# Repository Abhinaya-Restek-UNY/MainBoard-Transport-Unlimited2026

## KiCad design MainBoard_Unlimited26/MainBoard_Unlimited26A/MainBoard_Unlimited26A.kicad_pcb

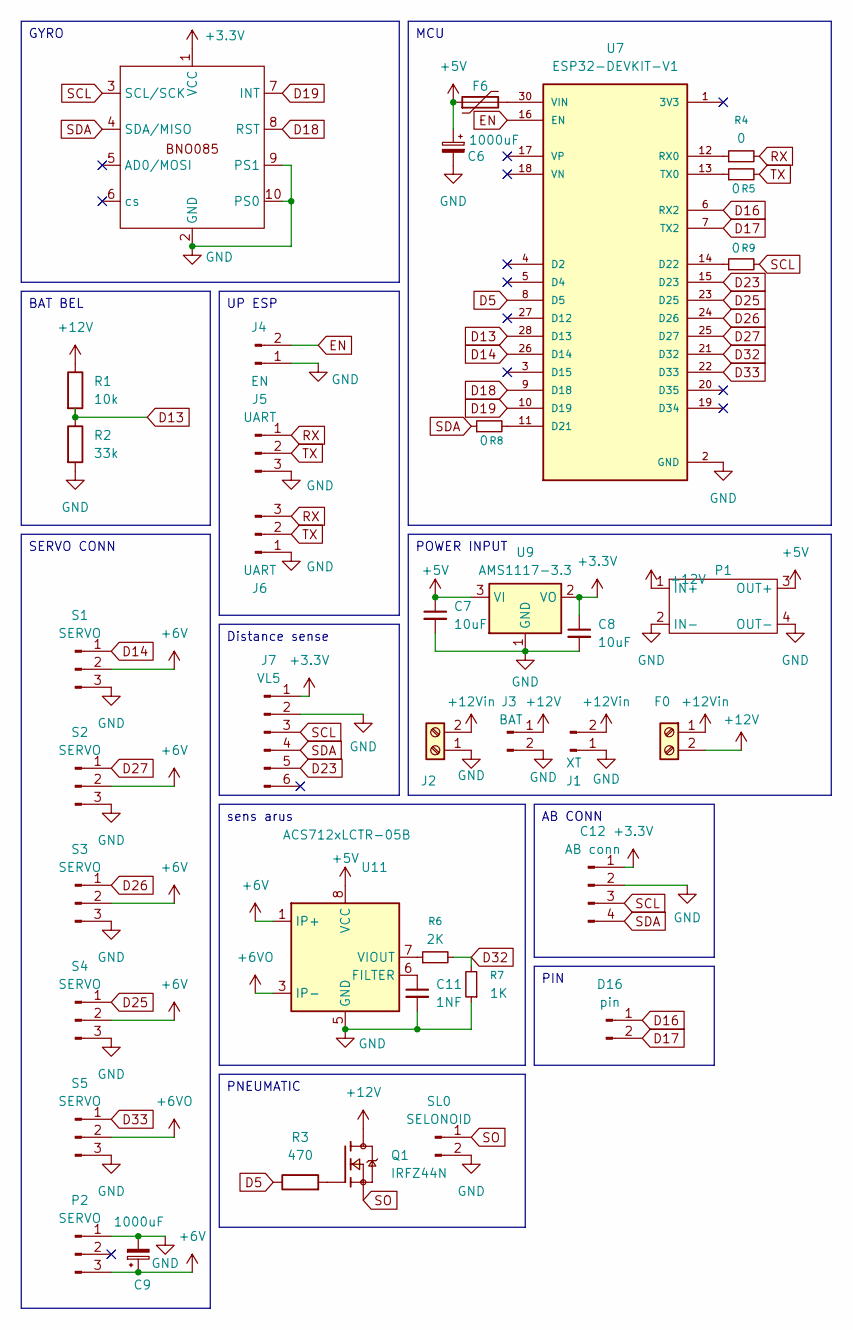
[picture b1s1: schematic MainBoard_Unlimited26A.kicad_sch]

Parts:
C6, C9: 1000uF; CP_Radial_D10.0mm_P5.00mm
C7, C8: 10uF; C_0805_2012Metric_Pad1.18x1.45mm_HandSolder
C11: 1NF; C_0805_2012Metric_Pad1.18x1.45mm_HandSolder
C12: AB conn; JST_XH_S4B-XH-A-1_1x04_P2.50mm_Horizontal
D16: pin; PinHeader_1x02_P2.54mm_Vertical
F0: Screw_Terminal_01x02; TerminalBlock_MaiXu_MX126-5.0-02P_1x02_P5.00mm
F6: Polyfuse; Fuse_1812_4532Metric
J1: XT; AMASS_XT60-M_1x02_P7.20mm_Vertical
J2: Screw_Terminal_01x02; TerminalBlock_MaiXu_MX126-5.0-02P_1x02_P5.00mm
J3: BAT; JST_XH_B2B-XH-A_1x02_P2.50mm_Vertical
J4: EN; PinHeader_1x02_P2.54mm_Horizontal
J5: UART; PinHeader_1x03_P2.54mm_Horizontal
J6: UART; JST_XH_S3B-XH-A_1x03_P2.50mm_Horizontal
J7: VL5; JST_XH_B6B-XH-A_1x06_P2.50mm_Vertical
P1: MP1584_Module
P2: SERVO; JST_XH_B3B-XH-A_1x03_P2.50mm_Vertical
Q1: IRFZ44N; TO254P1016X419X2286-3; PARTREV 09/21/10
R1: 10k; R_1206_3216Metric_Pad1.30x1.75mm_HandSolder
R2: 33k; R_0805_2012Metric_Pad1.20x1.40mm_HandSolder
R3: 470; R_1206_3216Metric_Pad1.30x1.75mm_HandSolder
R4, R5, R8, R9: 0; R_1206_3216Metric_Pad1.30x1.75mm_HandSolder
R6: 2K; R_0805_2012Metric_Pad1.20x1.40mm_HandSolder
R7: 1K; R_0805_2012Metric_Pad1.20x1.40mm_HandSolder
S1, S2, S3, S4, S5: SERVO; JST_XH_B3B-XH-A_1x03_P2.50mm_Vertical
SL0: SELONOID; JST_XH_B2B-XH-A_1x02_P2.50mm_Vertical
U7: ESP32-DEVKIT-V1; MODULE_ESP32_DEVKIT_V1; PARTREV N/A
U8: MPU6050/BNO085 I2C; PinSocket_1x10_P2.54mm_Vertical
U9: AMS1117-3.3; SOT-223-3_TabPin2
U11: ACS712xLCTR-05B; SOIC-8_3.9x4.9mm_P1.27mm

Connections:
+3.3V: C8.1, C12.1, J7.1, U8.1 (VCC), U9.2 (VO)
+5V: C6.1, C7.1, F6.1, P1.3 (OUT+), U9.3 (VI), U11.8 (VCC)
+6V: C9.1, P2.3, S1.2, S2.2, S3.2, S4.2, U11.1 (IP+), U11.2 (IP+)
+6VO: S5.2, U11.3 (IP-), U11.4 (IP-)
+12V: F0.2, J3.1, P1.1 (IN+), Q1.2, R1.1
+12Vin: F0.1, J1.2, J2.2
D5: R3.1, U7.8 (D5)
D13: R1.2, R2.1, U7.28 (D13)
D14: S1.1, U7.26 (D14)
D16: D16.1, U7.6 (RX2)
D17: D16.2, U7.7 (TX2)
D18: U7.9 (D18), U8.8 (RST)
D19: U7.10 (D19), U8.7 (INT)
D23: J7.5, U7.15 (D23)
D25: S4.1, U7.23 (D25)
D26: S3.1, U7.24 (D26)
D27: S2.1, U7.25 (D27)
D32: R6.2, R7.2, U7.21 (D32)
D33: S5.1, U7.22 (D33)
EN: J4.2, U7.16 (EN)
GND: C6.2, C7.2, C8.2, C9.2, C11.2, C12.2, J1.1, J2.1, J3.2, J4.1, J5.3, J6.1, J7.2, P1.2 (IN-), P1.4 (OUT-), P2.1, R2.2, R7.1, S1.3, S2.3, S3.3, S4.3, S5.3, SL0.2, U7.2 (GND), U7.29 (GND), U8.2 (GND), U8.9 (PS1), U8.10 (PS0), U9.1 (GND), U11.5 (GND)
unnamed: Q1.1, R3.2
unnamed: R8.2, U7.11 (D21)
unnamed: R9.1, U7.14 (D22)
unnamed: R4.1, U7.12 (RX0)
unnamed: R5.1, U7.13 (TX0)
unnamed: F6.2, U7.30 (VIN)
unnamed: C11.1, U11.6 (FILTER)
unnamed: R6.1, U11.7 (VIOUT)
RX: J5.1, J6.3, R4.2
SCL: C12.3, J7.3, R9.2, U8.3 (SCL/SCK)
SDA: C12.4, J7.4, R8.1, U8.4 (SDA/MISO)
SO: Q1.3, SL0.1
TX: J5.2, J6.2, R5.2

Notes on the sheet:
AB CONN
PIN
UP ESP
PNEUMATIC
sens arus
POWER INPUT
MCU
BAT BEL
Distance sense
GYRO
SERVO CONN

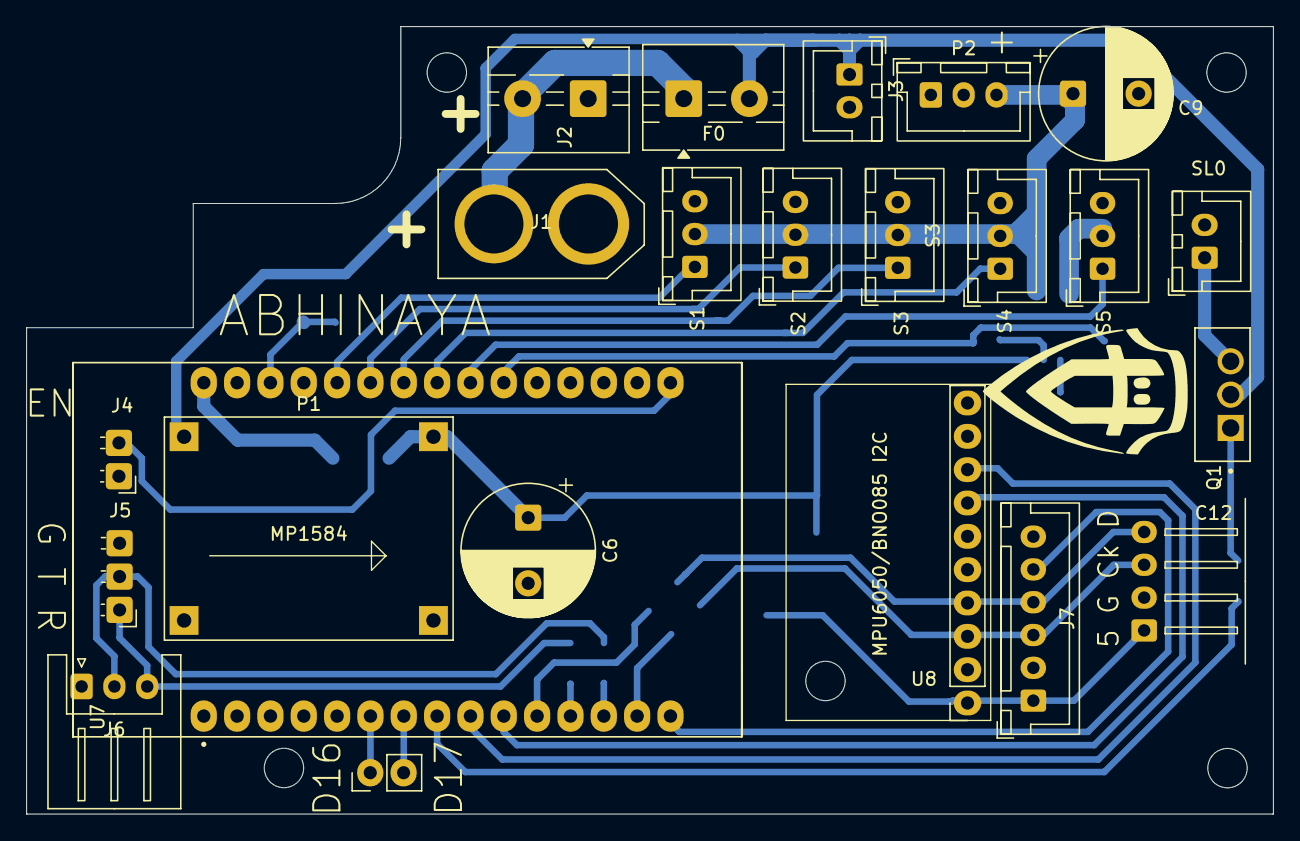
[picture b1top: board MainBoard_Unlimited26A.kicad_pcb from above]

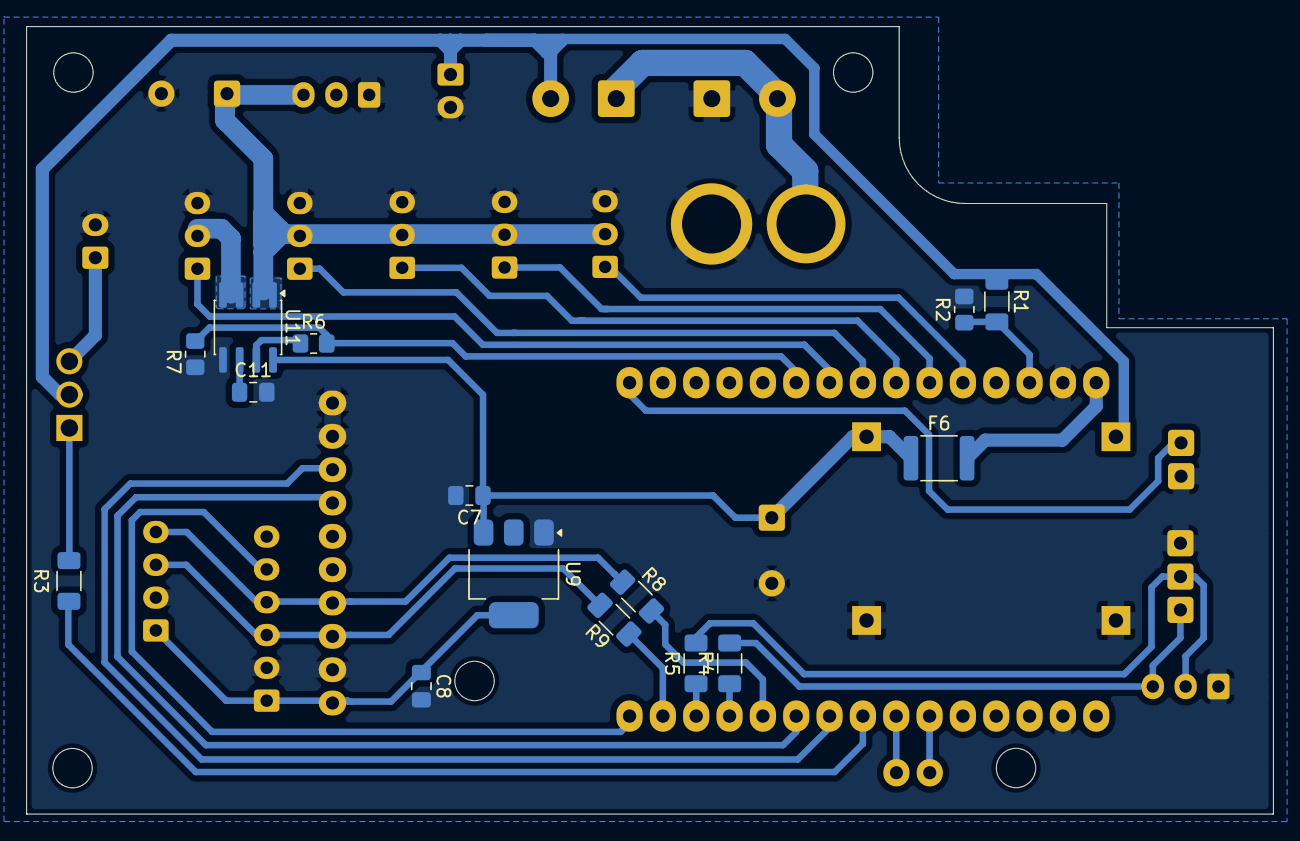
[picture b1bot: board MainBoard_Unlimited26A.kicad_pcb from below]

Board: 2 copper layers, 95.0 x 60.0 mm, 38 parts (15 on the bottom side), 34 nets.

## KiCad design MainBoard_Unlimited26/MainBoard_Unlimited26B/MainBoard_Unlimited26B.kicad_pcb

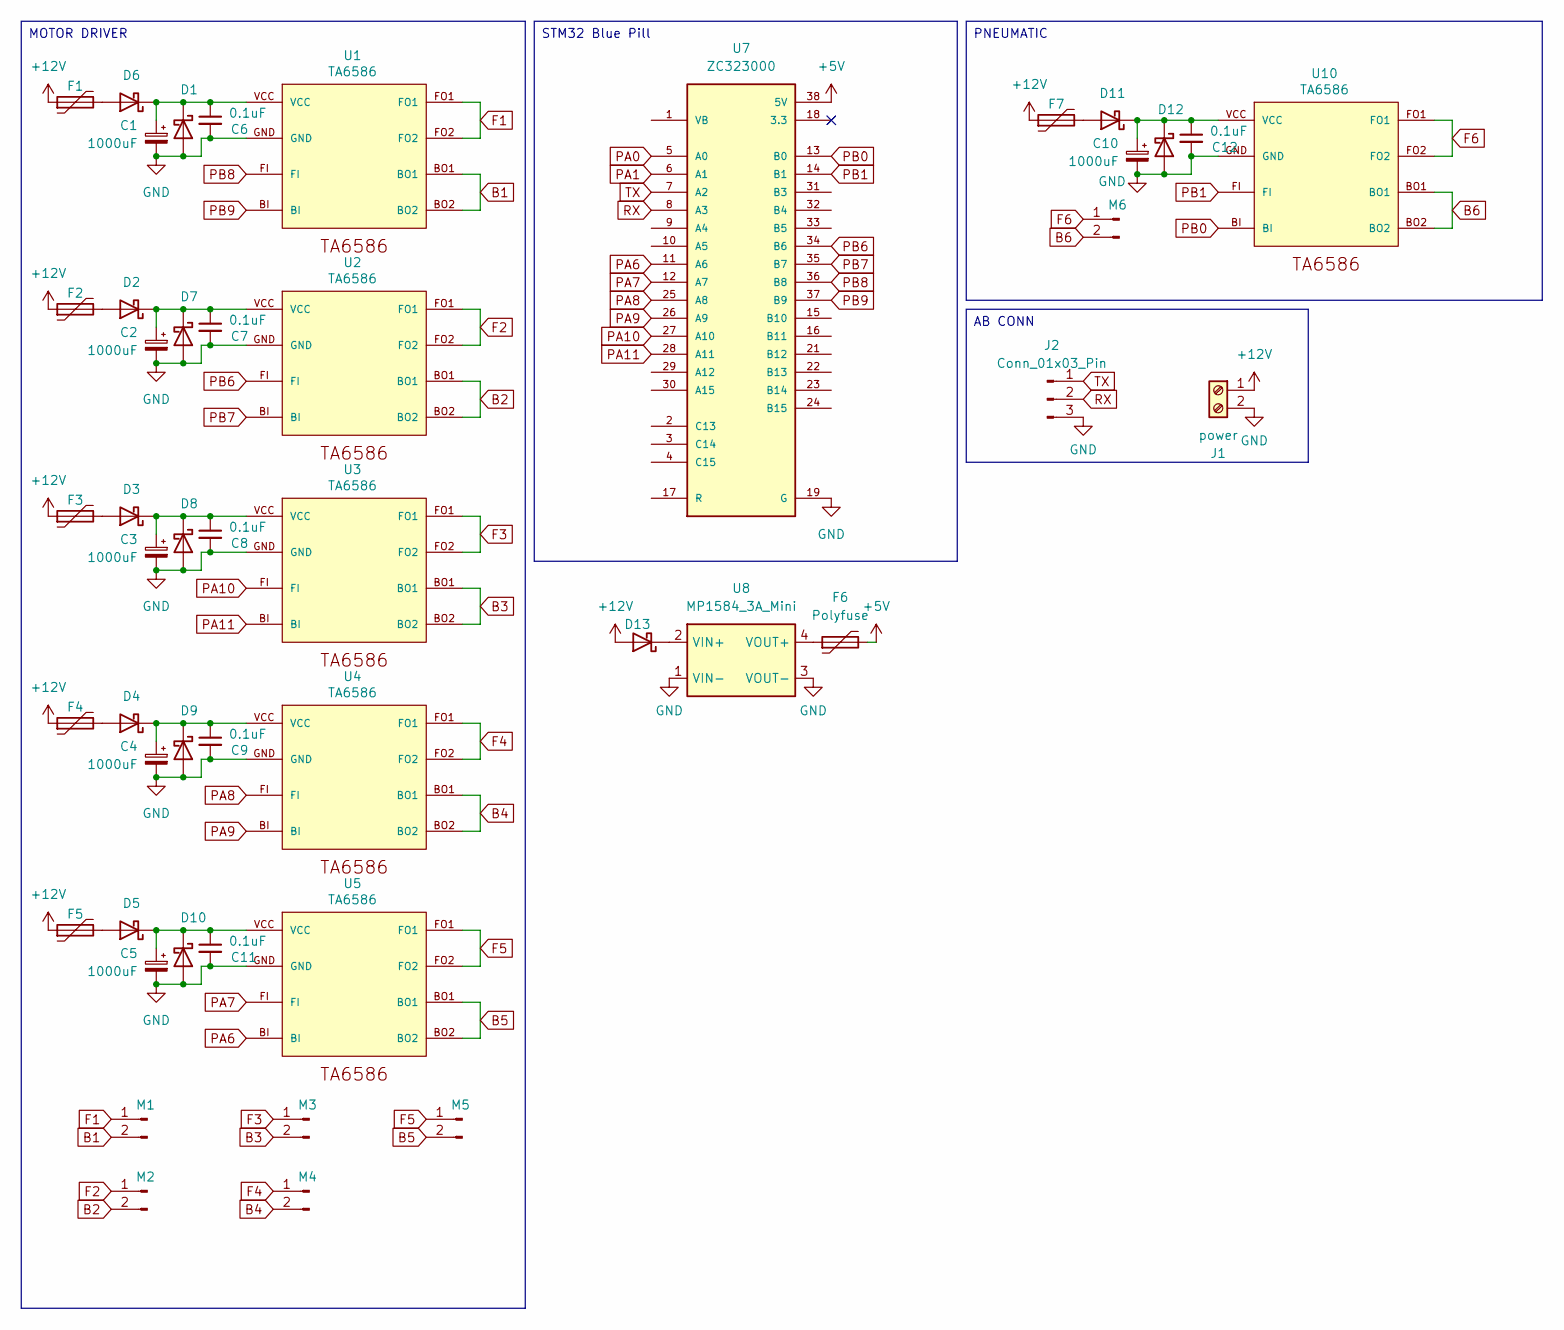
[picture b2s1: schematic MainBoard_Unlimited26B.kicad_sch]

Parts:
C1, C2, C3, C4, C5, C10: 1000uF; CP_Radial_D10.0mm_P5.00mm
C6, C7, C8, C9, C11, C12: 0.1uF; C_0805_2012Metric_Pad1.18x1.45mm_HandSolder
D1, D2, D3, D4, D5, D6, D7, D8, D9, D10, D11, D12, D13: D_Schottky; D_SMA
F1, F2, F3, F4, F5, F7: Polyfuse; Fuse_Bourns_MF-RG300
F6: Polyfuse; Fuse_1812_4532Metric
J1: power; TE_282815-2
J2: Conn_01x03_Pin; JST_XH_B3B-XH-A_1x03_P2.50mm_Vertical
M1, M2, M3, M4, M5, M6: JST_XH_S2B-XH-A-1_1x02_P2.50mm_Horizontal
U1, U2, U3, U4, U5, U10: TA6586; TA6586-FOOTPRINT
U7: ZC323000; MODULE_ZC323000; PARTREV N/A
U8: MP1584_3A_Mini; Mini360

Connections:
+5V: F6.2, U7.38 (5V)
+12V: D13.2 (A), F1.1, F2.1, F3.1, F4.1, F5.1, F7.1, J1.1
B1: M1.2, U1.BO1, U1.BO2
B2: M2.2, U2.BO1, U2.BO2
B3: M3.2, U3.BO1, U3.BO2
B4: M4.2, U4.BO1, U4.BO2
B5: M5.2, U5.BO1, U5.BO2
B6: M6.2, U10.BO1, U10.BO2
F1: M1.1, U1.FO1, U1.FO2
F2: M2.1, U2.FO1, U2.FO2
F3: M3.1, U3.FO1, U3.FO2
F4: M4.1, U4.FO1, U4.FO2
F5: M5.1, U5.FO1, U5.FO2
F6: M6.1, U10.FO1, U10.FO2
GND: C1.2, C2.2, C3.2, C4.2, C5.2, C6.2, C7.2, C8.2, C9.2, C10.2, C11.2, C12.2, D1.2 (A), D7.2 (A), D8.2 (A), D9.2 (A), D10.2 (A), D12.2 (A), J1.2, J2.3, U1.GND, U2.GND, U3.GND, U4.GND, U5.GND, U7.19 (G), U7.20 (G), U7.39 (G), U8.1 (VIN-), U8.3 (VOUT-), U10.GND
unnamed: C1.1, C6.1, D1.1 (K), D6.1 (K), U1.VCC
unnamed: D2.2 (A), F2.2
unnamed: C2.1, C7.1, D2.1 (K), D7.1 (K), U2.VCC
unnamed: D3.2 (A), F3.2
unnamed: C3.1, C8.1, D3.1 (K), D8.1 (K), U3.VCC
unnamed: D4.2 (A), F4.2
unnamed: C4.1, C9.1, D4.1 (K), D9.1 (K), U4.VCC
unnamed: D5.2 (A), F5.2
unnamed: D6.2 (A), F1.2
unnamed: C5.1, C11.1, D5.1 (K), D10.1 (K), U5.VCC
unnamed: D11.2 (A), F7.2
unnamed: C10.1, C12.1, D11.1 (K), D12.1 (K), U10.VCC
unnamed: D13.1 (K), U8.2 (VIN+)
unnamed: F6.1, U8.4 (VOUT+)
PA0: U7.5 (A0)
PA1: U7.6 (A1)
PA6: U5.BI, U7.11 (A6)
PA7: U5.FI, U7.12 (A7)
PA8: U4.FI, U7.25 (A8)
PA9: U4.BI, U7.26 (A9)
PA10: U3.FI, U7.27 (A10)
PA11: U3.BI, U7.28 (A11)
PB0: U7.13 (B0), U10.BI
PB1: U7.14 (B1), U10.FI
PB6: U2.FI, U7.34 (B6)
PB7: U2.BI, U7.35 (B7)
PB8: U1.FI, U7.36 (B8)
PB9: U1.BI, U7.37 (B9)
RX: J2.2, U7.8 (A3)
TX: J2.1, U7.7 (A2)

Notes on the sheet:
PNEUMATIC
AB CONN
MOTOR DRIVER
STM32 Blue Pill

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
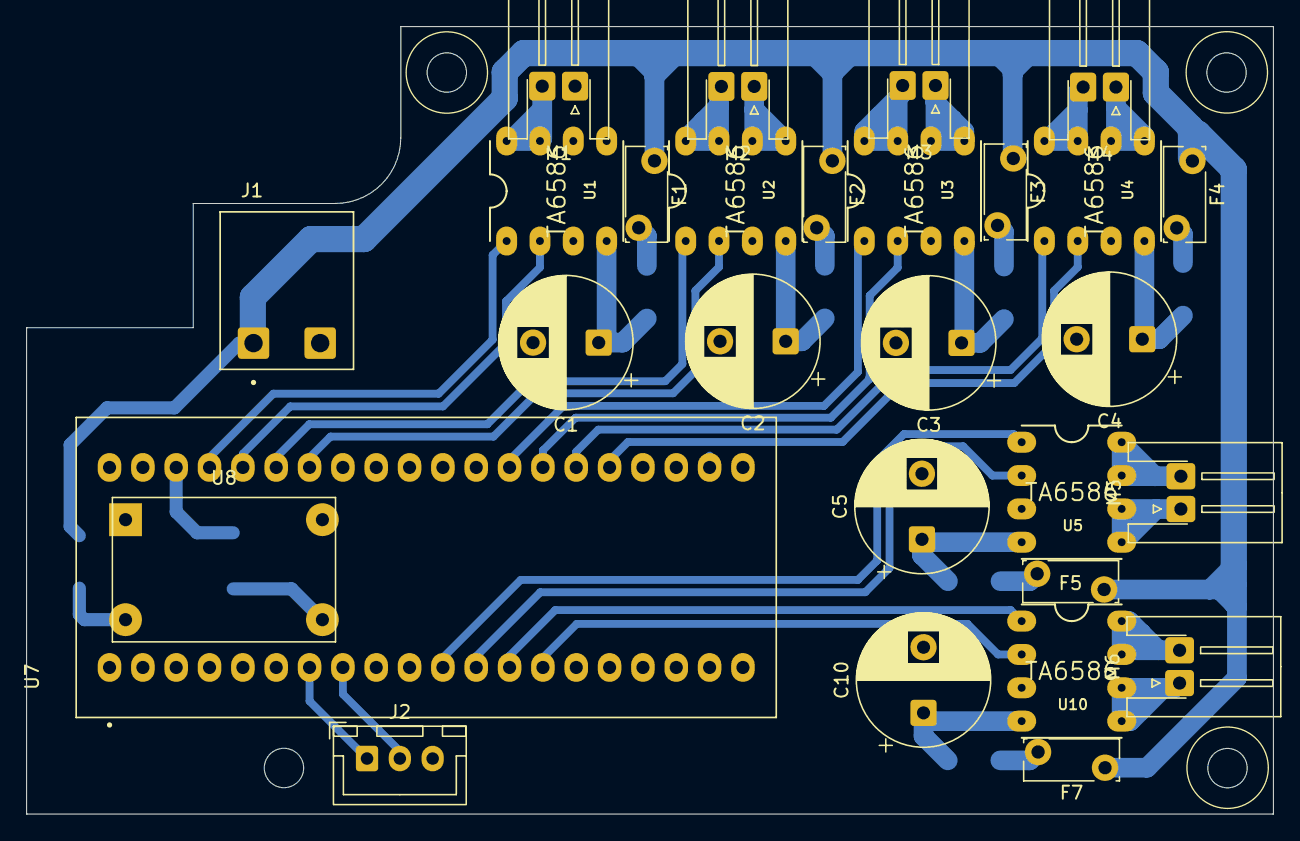
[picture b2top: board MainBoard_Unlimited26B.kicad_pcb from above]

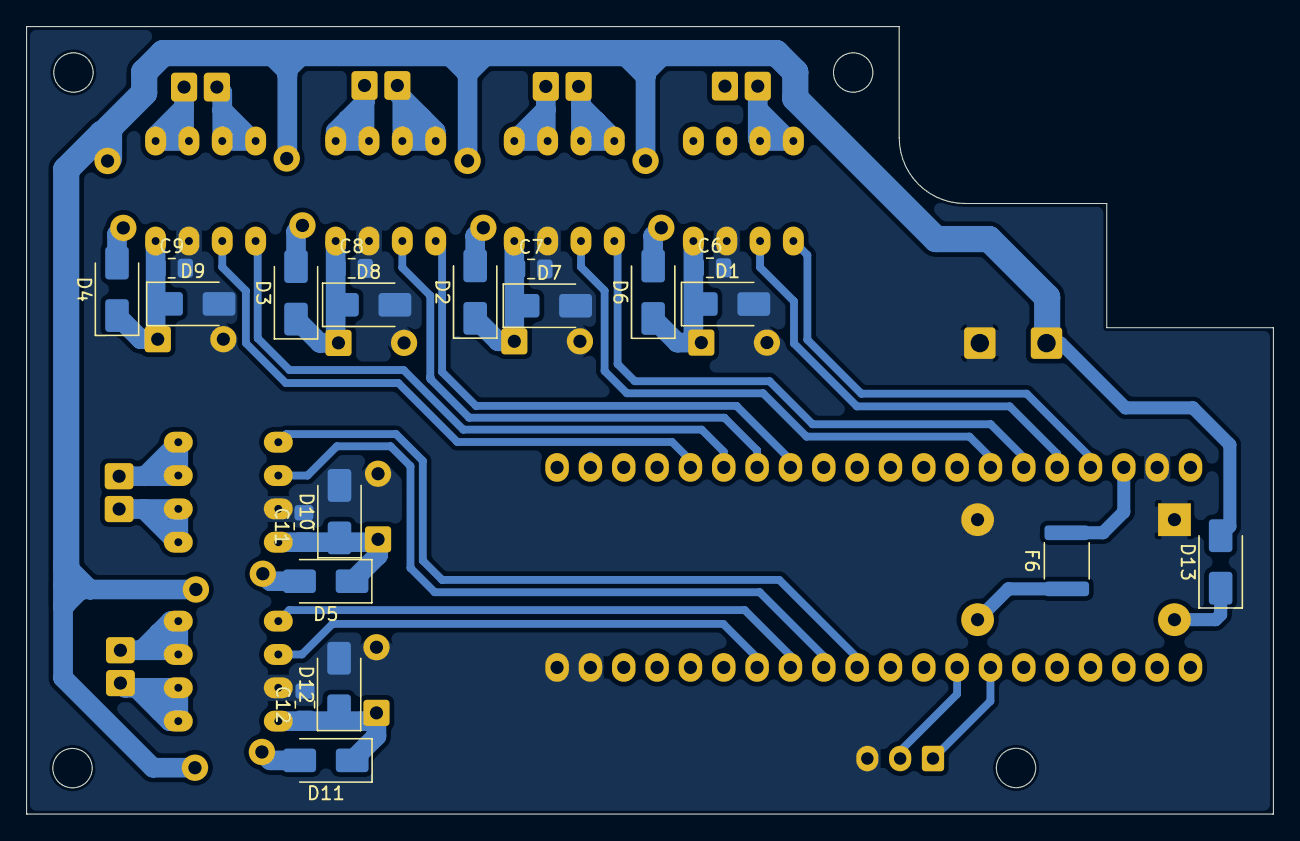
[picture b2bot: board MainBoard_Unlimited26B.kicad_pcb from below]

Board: 2 copper layers, 95.0 x 60.0 mm, 48 parts (20 on the bottom side), 43 nets.

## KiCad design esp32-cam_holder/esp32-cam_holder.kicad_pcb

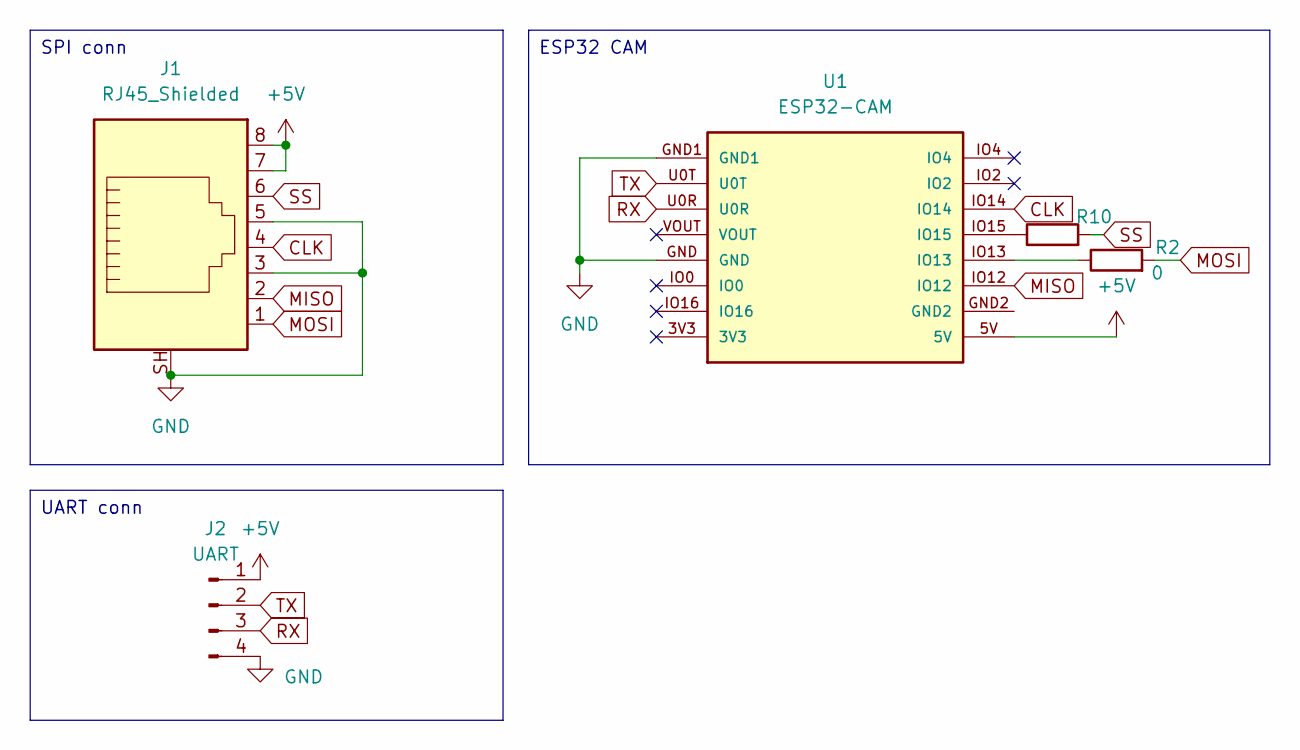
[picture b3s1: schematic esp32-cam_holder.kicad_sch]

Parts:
J1: RJ45_Shielded; RJ45_Amphenol_RJHSE5380
J2: UART; PinHeader_1x04_P2.54mm_Horizontal
R1, R2: 0; R_1206_3216Metric_Pad1.30x1.75mm_HandSolder
U1: ESP32-CAM

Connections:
+5V: J1.7, J1.8, J2.1, U1.5V
CLK: J1.4, U1.IO14
GND: J1.3, J1.5, J1.SH, J2.4, U1.GND, U1.GND1
MISO: J1.2, U1.IO12
MOSI: J1.1, R2.2
unnamed: R1.1, U1.IO15
unnamed: R2.1, U1.IO13
RX: J2.3, U1.U0R
SS: J1.6, R1.2
TX: J2.2, U1.U0T

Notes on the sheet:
ESP32 CAM
SPI conn
UART conn

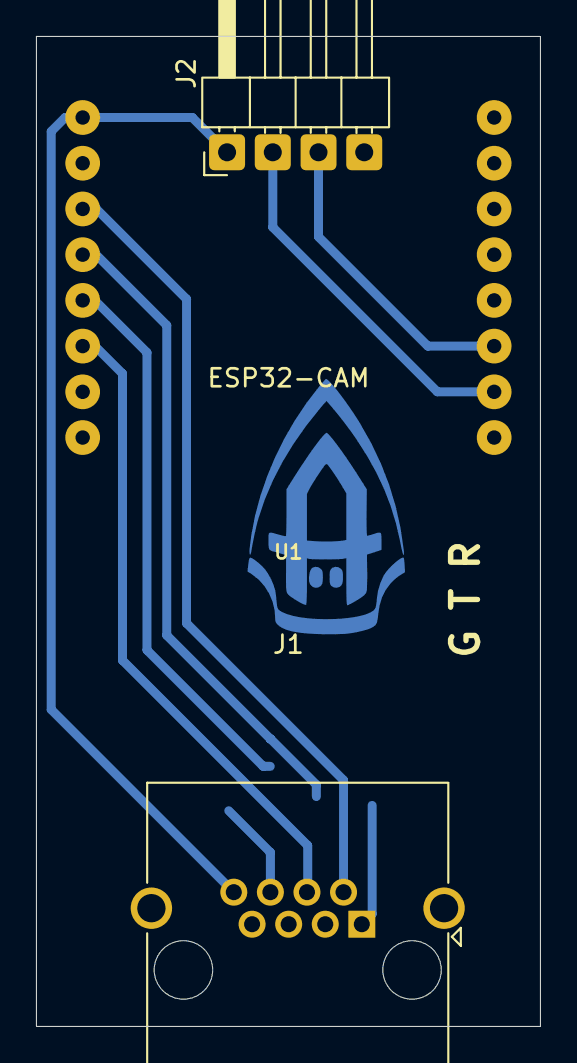
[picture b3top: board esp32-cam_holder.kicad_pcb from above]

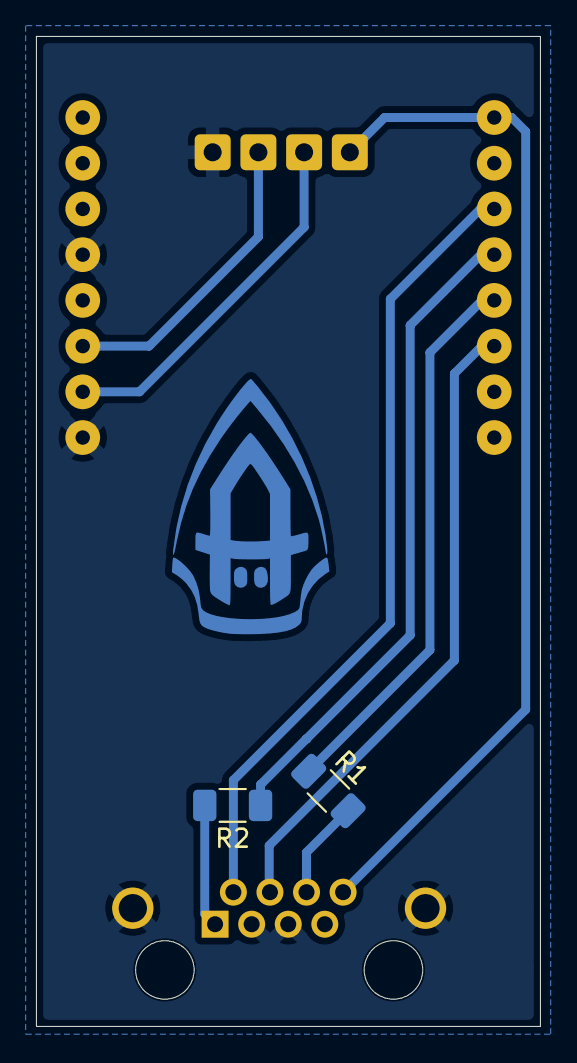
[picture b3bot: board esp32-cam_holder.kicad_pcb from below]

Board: 2 copper layers, 28.0 x 55.0 mm, 5 parts (2 on the bottom side), 10 nets.

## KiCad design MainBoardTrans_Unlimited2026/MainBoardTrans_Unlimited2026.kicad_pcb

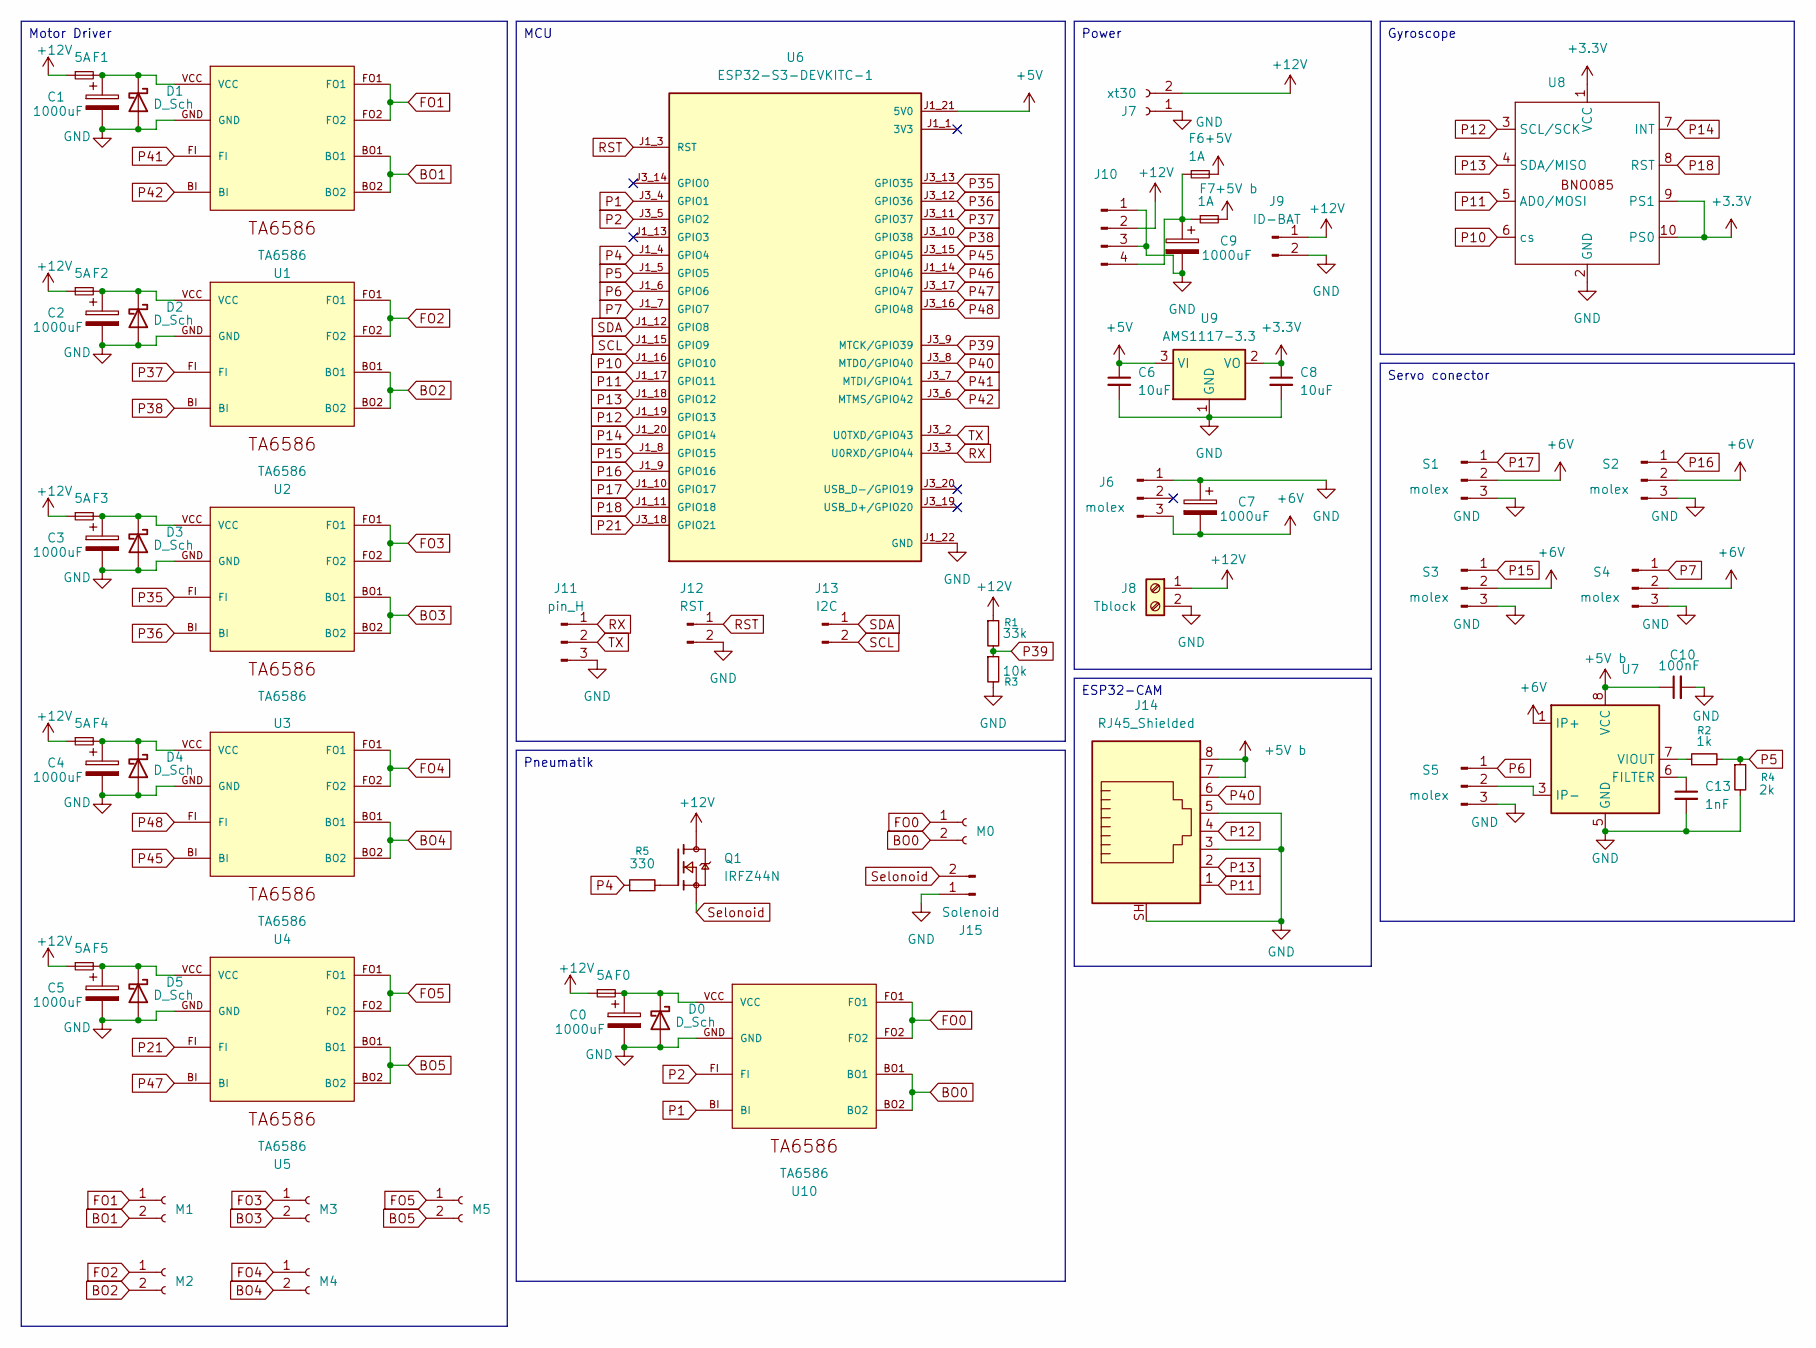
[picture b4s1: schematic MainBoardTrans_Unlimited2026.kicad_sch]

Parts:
C0, C1, C2, C3, C4, C5, C7, C9: 1000uF; CP_Radial_D10.0mm_P5.00mm
C6, C8: 10uF; C_0805_2012Metric_Pad1.18x1.45mm_HandSolder
C10: 100nF; C_0805_2012Metric_Pad1.18x1.45mm_HandSolder
C13: 1nF; C_0805_2012Metric_Pad1.18x1.45mm_HandSolder
D0, D1, D2, D3, D4, D5: D_Sch; D_SMA_Handsoldering
F0, F1, F2, F3, F4, F5: 5A; Fuse_Bourns_MF-RHT300
F6, F7: 1A; Fuse_1812_4532Metric
J6: molex; JST_XH_B3B-XH-A_1x03_P2.50mm_Vertical
J7: xt30; AMASS_XT30U-M_1x02_P5.0mm_Vertical
J8: Tblock; TerminalBlock_MaiXu_MX126-5.0-02P_1x02_P5.00mm
J9: ID-BAT; JST_XH_B2B-XH-A_1x02_P2.50mm_Vertical
J10: DSN-MINI-360; Mini360
J11: pin_H; PinHeader_1x03_P2.54mm_Horizontal
J12: RST; JST_XH_B2B-XH-A_1x02_P2.50mm_Vertical
J13: I2C; PinHeader_1x02_P2.54mm_Vertical
J14: RJ45_Shielded; RJ45_Amphenol_RJHSE5380
J15: Solenoid; JST_XH_B2B-XH-A_1x02_P2.50mm_Vertical
M0, M1, M2, M3, M4, M5: TerminalBlock_MaiXu_MX126-5.0-02P_1x02_P5.00mm
Q1: IRFZ44N; TO254P1016X419X2286-3; PARTREV 09/21/10
R1: 33k; R_Axial_DIN0207_L6.3mm_D2.5mm_P10.16mm_Horizontal
R2: 1k; R_0805_2012Metric_Pad1.20x1.40mm_HandSolder
R3: 10k; R_Axial_DIN0207_L6.3mm_D2.5mm_P10.16mm_Horizontal
R4: 2k; R_0805_2012Metric_Pad1.20x1.40mm_HandSolder
R5: 330; R_1206_3216Metric_Pad1.30x1.75mm_HandSolder
S1, S2, S3, S4, S5: molex; JST_XH_B3B-XH-A_1x03_P2.50mm_Vertical
U1, U2, U3, U4, U5, U10: TA6586; TA6586-FOOTPRINT
U6: ESP32-S3-DEVKITC-1; XCVR_ESP32-S3-DEVKITC-1-N32R8V; PARTREV 1.1
U7: ACS712xLCTR-05B; SOIC-8_3.9x4.9mm_P1.27mm
U8: BNO085
U9: AMS1117-3.3; SOT-223-3_TabPin2

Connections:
+3.3V: C8.1, U8.1 (VCC), U8.9 (PS1), U8.10 (PS0), U9.2 (VO)
+5V: C6.1, F6.2, U6.J1_21 (5V0), U9.3 (VI)
+5V b: C10.1, F7.2, J14.7, J14.8, U7.8 (VCC)
+6V: C7.2, J6.3, S1.2, S2.2, S3.2, S4.2, U7.1 (IP+), U7.2 (IP+)
+12V: F0.1, F1.1, F2.1, F3.1, F4.1, F5.1, J7.2, J8.1, J9.1, J10.2, Q1.2, R1.1
BO0: M0.2, U10.BO1, U10.BO2
BO1: M1.2, U1.BO1, U1.BO2
BO2: M2.2, U2.BO1, U2.BO2
BO3: M3.2, U3.BO1, U3.BO2
BO4: M4.2, U4.BO1, U4.BO2
BO5: M5.2, U5.BO1, U5.BO2
FO0: M0.1, U10.FO1, U10.FO2
FO1: M1.1, U1.FO1, U1.FO2
FO2: M2.1, U2.FO1, U2.FO2
FO3: M3.1, U3.FO1, U3.FO2
FO4: M4.1, U4.FO1, U4.FO2
FO5: M5.1, U5.FO1, U5.FO2
GND: C0.2, C1.2, C2.2, C3.2, C4.2, C5.2, C6.2, C7.1, C8.2, C9.2, C10.2, C13.2, D0.2 (A), D1.2 (A), D2.2 (A), D3.2 (A), D4.2 (A), D5.2 (A), J6.1, J7.1, J8.2, J9.2, J10.1, J10.3, J11.3, J12.2, J14.3, J14.5, J14.SH, J15.1, R3.2, R4.2, S1.3, S2.3, S3.3, S4.3, S5.3, U1.GND, U2.GND, U3.GND, U4.GND, U5.GND, U6.J1_22 (GND), U6.J3_1 (GND), U6.J3_21 (GND), U6.J3_22 (GND), U7.5 (GND), U8.2 (GND), U9.1 (GND), U10.GND
unnamed: C0.1, D0.1 (K), F0.2, U10.VCC
unnamed: C1.1, D1.1 (K), F1.2, U1.VCC
unnamed: C2.1, D2.1 (K), F2.2, U2.VCC
unnamed: C3.1, D3.1 (K), F3.2, U3.VCC
unnamed: C4.1, D4.1 (K), F4.2, U4.VCC
unnamed: C5.1, D5.1 (K), F5.2, U5.VCC
unnamed: C9.1, F6.1, F7.1, J10.4
unnamed: Q1.1, R5.2
unnamed: S5.2, U7.3 (IP-), U7.4 (IP-)
unnamed: C13.1, U7.6 (FILTER)
unnamed: R2.1, U7.7 (VIOUT)
P1: U6.J3_4 (GPIO1), U10.BI
P2: U6.J3_5 (GPIO2), U10.FI
P4: R5.1, U6.J1_4 (GPIO4)
P5: R2.2, R4.1, U6.J1_5 (GPIO5)
P6: S5.1, U6.J1_6 (GPIO6)
P7: S4.1, U6.J1_7 (GPIO7)
P10: U6.J1_16 (GPIO10), U8.6 (cs)
P11: J14.1, U6.J1_17 (GPIO11), U8.5 (AD0/MOSI)
P12: J14.4, U6.J1_19 (GPIO13), U8.3 (SCL/SCK)
P13: J14.2, U6.J1_18 (GPIO12), U8.4 (SDA/MISO)
P14: U6.J1_20 (GPIO14), U8.7 (INT)
P15: S3.1, U6.J1_8 (GPIO15)
P16: S2.1, U6.J1_9 (GPIO16)
P17: S1.1, U6.J1_10 (GPIO17)
P18: U6.J1_11 (GPIO18), U8.8 (RST)
P21: U5.FI, U6.J3_18 (GPIO21)
P35: U3.FI, U6.J3_13 (GPIO35)
P36: U3.BI, U6.J3_12 (GPIO36)
P37: U2.FI, U6.J3_11 (GPIO37)
P38: U2.BI, U6.J3_10 (GPIO38)
P39: R1.2, R3.1, U6.J3_9 (MTCK/GPIO39)
P40: J14.6, U6.J3_8 (MTDO/GPIO40)
P41: U1.FI, U6.J3_7 (MTDI/GPIO41)
P42: U1.BI, U6.J3_6 (MTMS/GPIO42)
P45: U4.BI, U6.J3_15 (GPIO45)
P46: U6.J1_14 (GPIO46)
P47: U5.BI, U6.J3_17 (GPIO47)
P48: U4.FI, U6.J3_16 (GPIO48)
RST: J12.1, U6.J1_3 (RST)
RX: J11.1, U6.J3_3 (U0RXD/GPIO44)
SCL: J13.2, U6.J1_15 (GPIO9)
SDA: J13.1, U6.J1_12 (GPIO8)
Selonoid: J15.2, Q1.3
TX: J11.2, U6.J3_2 (U0TXD/GPIO43)

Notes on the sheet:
Pneumatik
Motor Driver
Gyroscope
MCU
Servo conector
Power
ESP32-CAM

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
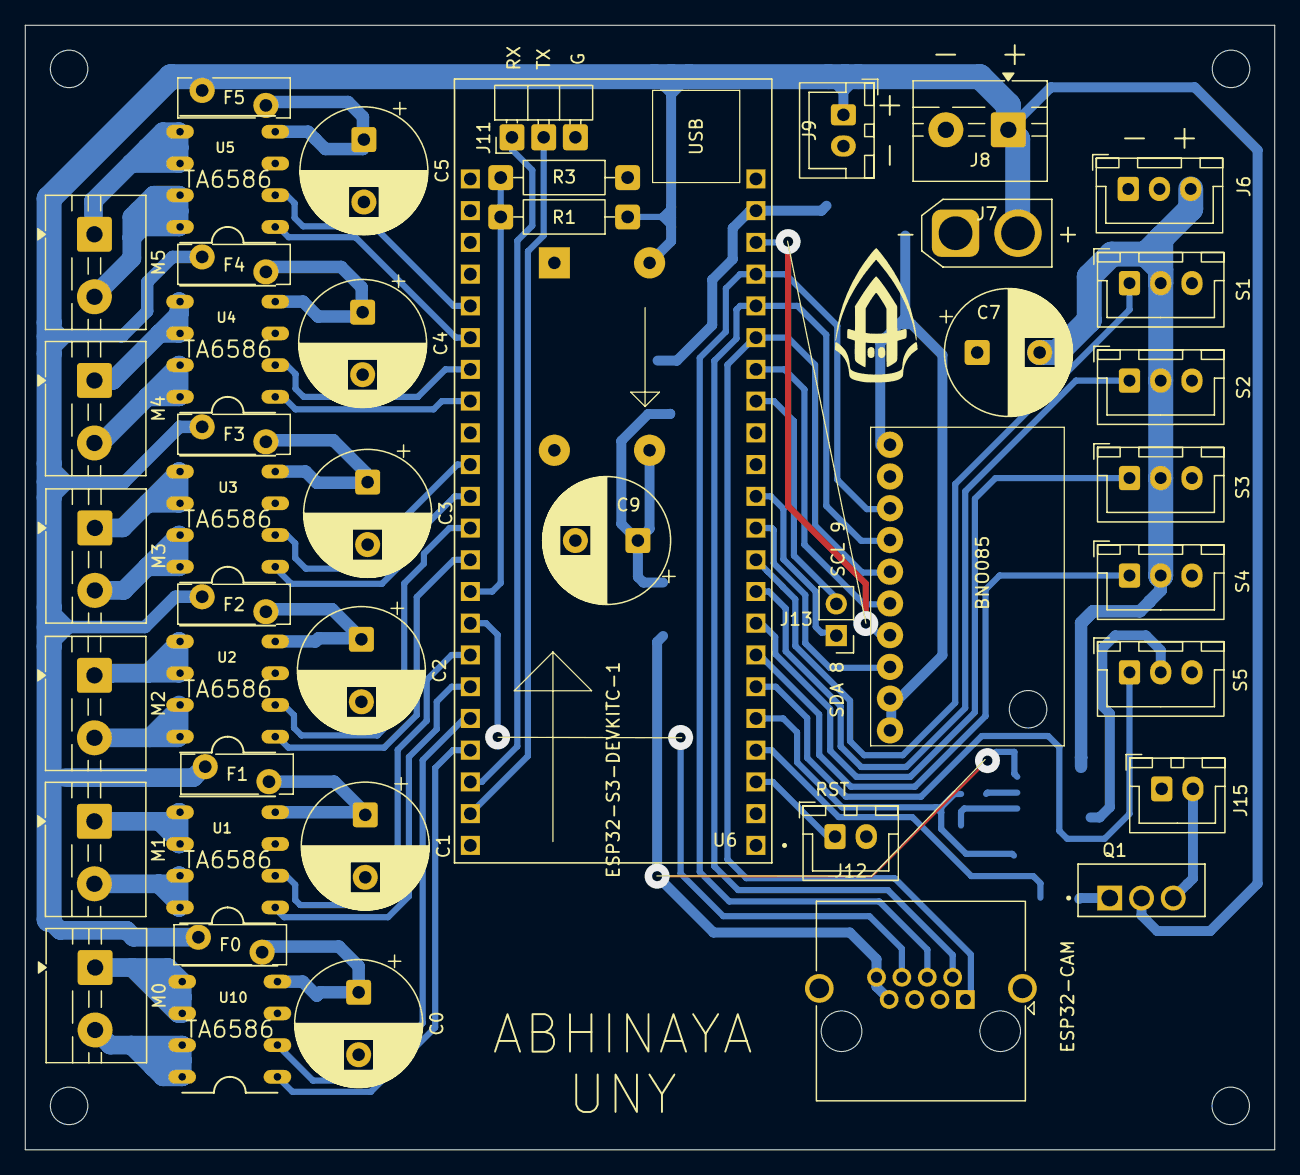
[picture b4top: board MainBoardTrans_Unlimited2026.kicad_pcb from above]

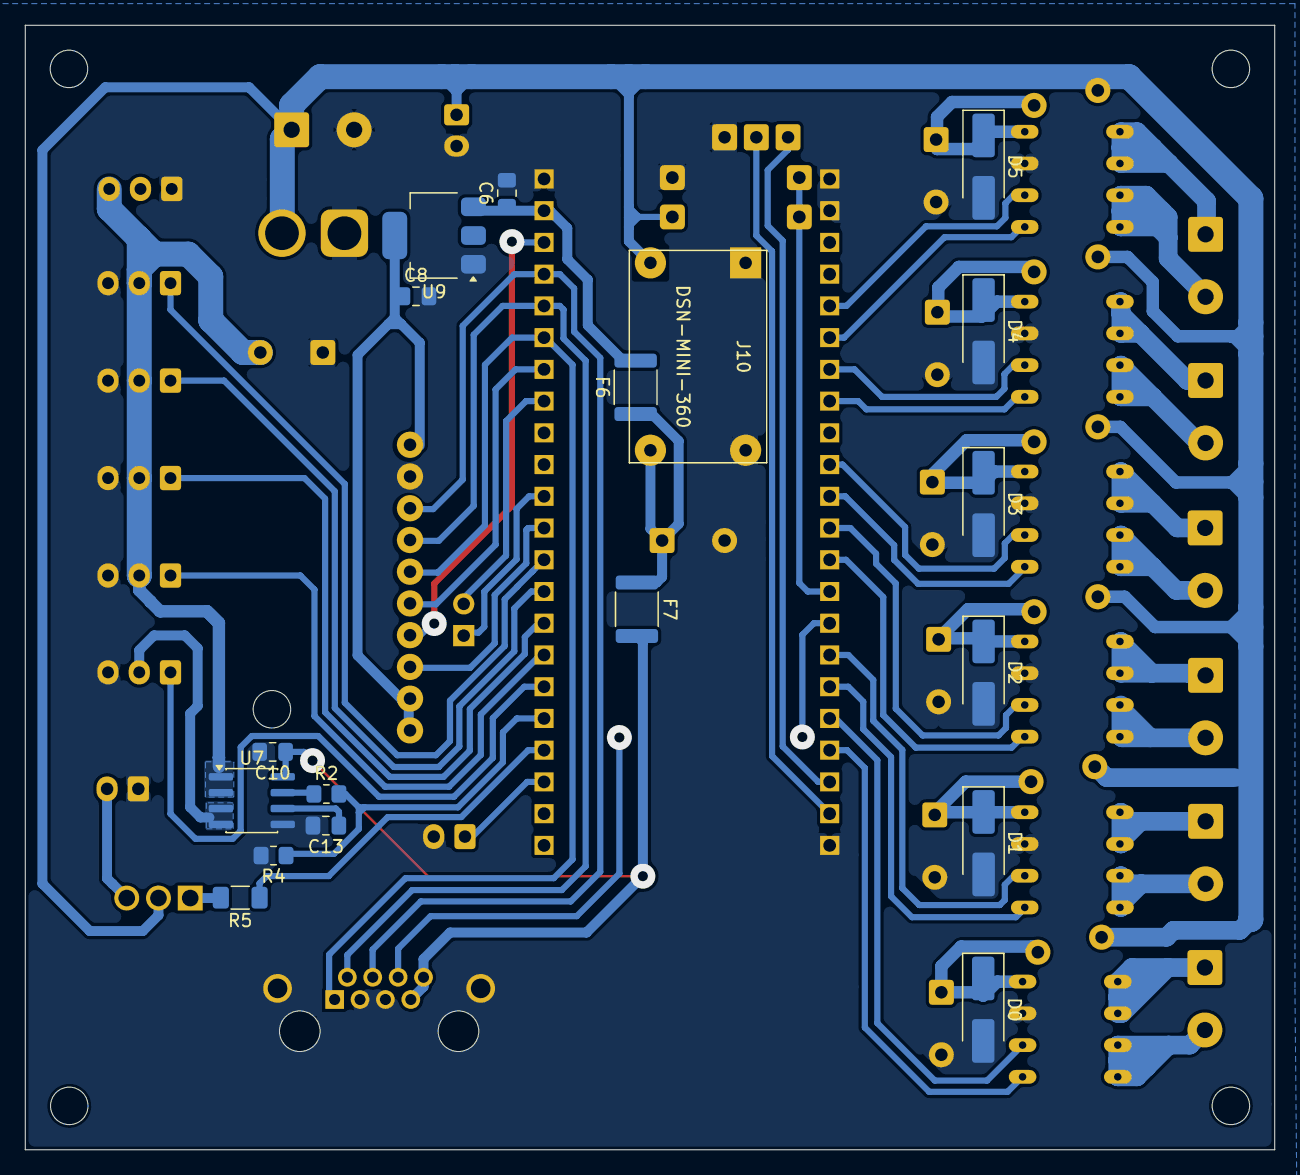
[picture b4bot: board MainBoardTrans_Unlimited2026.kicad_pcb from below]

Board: 2 copper layers, 100.0 x 90.0 mm, 63 parts (18 on the bottom side), 62 nets.
